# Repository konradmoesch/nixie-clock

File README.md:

# nixie-clock
6-digit nixie-clock using ESP32, IN-4 and IN-6

## dependencies
https://github.com/judge2005/Eagle-and-KiCAD-Nixie-Libs
https://github.com/Hieromon/AutoConnect

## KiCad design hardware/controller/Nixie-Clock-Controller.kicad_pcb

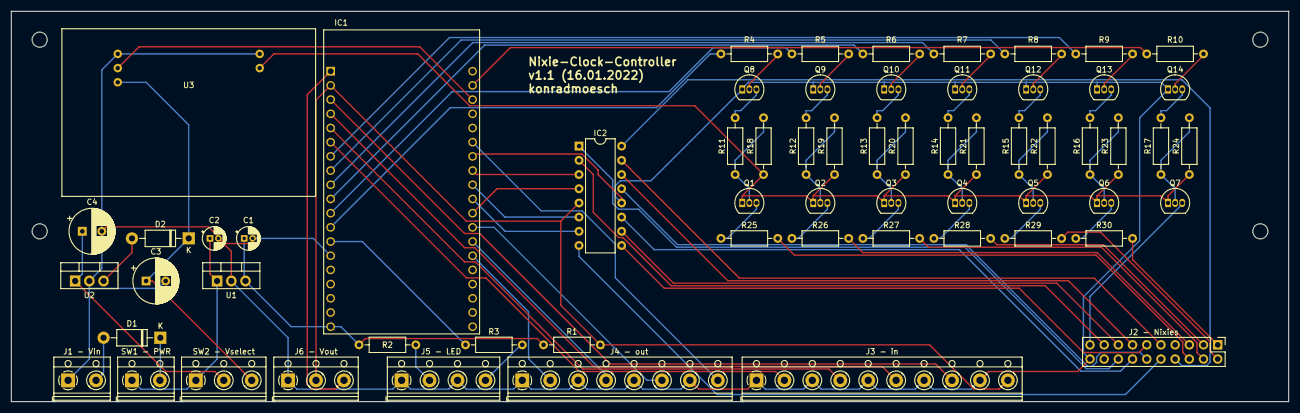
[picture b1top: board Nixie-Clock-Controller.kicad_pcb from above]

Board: 2 copper layers, 228.6 x 69.8 mm, 67 parts (0 on the bottom side), 78 nets.

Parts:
C1, C2: 10uF; CP_Radial_D4.0mm_P1.50mm
C3, C4: 100uF 50V; CP_Radial_D8.0mm_P3.50mm
D1, D2: 1N4001; D_DO-41_SOD81_P10.16mm_Horizontal
H1, H2, H3, H4: MountingHole; MountingHole_2.7mm_M2.5
IC1: ESP32-DEVKITC-V4; MODULE_ESP32-DEVKITC-32D
IC2: 74141; DIP-16_W7.62mm
J1 - Vin: 9/12-35V DC in; TerminalBlock_RND_205-00012_1x02_P5.00mm_Horizontal
J2 - Nixies: Nixies-Connector; PinHeader_2x10_P2.54mm_Vertical
J3 - in: Input; TerminalBlock_RND_205-00020_1x10_P5.00mm_Horizontal
J4 - out: Output; TerminalBlock_RND_205-00018_1x08_P5.00mm_Horizontal
J5 - LED: LEDs; TerminalBlock_RND_205-00014_1x04_P5.00mm_Horizontal
J6 - Vout: power_out; TerminalBlock_RND_205-00013_1x03_P5.00mm_Horizontal
Q1, Q2, Q3, Q4, Q5, Q6, Q7: MPSA92; TO-92_Inline
Q8, Q9, Q10, Q11, Q12, Q13, Q14: MPSA42; TO-92_Inline
R1: 1k; R_Axial_DIN0207_L6.3mm_D2.5mm_P10.16mm_Horizontal
R2, R3: 220R; R_Axial_DIN0207_L6.3mm_D2.5mm_P10.16mm_Horizontal
R4, R5, R6, R7, R8, R9, R10: 33k; R_Axial_DIN0207_L6.3mm_D2.5mm_P10.16mm_Horizontal
R11, R12, R13, R14, R15, R16, R17: 470k; R_Axial_DIN0207_L6.3mm_D2.5mm_P10.16mm_Horizontal
R18, R19, R20, R21, R22, R23, R24: 100k; R_Axial_DIN0207_L6.3mm_D2.5mm_P10.16mm_Horizontal
R25, R26, R27, R28, R29, R30: 10k; R_Axial_DIN0207_L6.3mm_D2.5mm_P10.16mm_Horizontal
SW1 - PWR: on/off; TerminalBlock_RND_205-00012_1x02_P5.00mm_Horizontal
SW2 - Vselect: in voltage select; TerminalBlock_RND_205-00013_1x03_P5.00mm_Horizontal
U1: L7805; TO-220-3_Vertical
U2: L7809; TO-220-3_Vertical
U3: NCH6300HV; NCH_6300_HV

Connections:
/a1: J2 - Nixies.1, R30.2
/a2: J2 - Nixies.2, R29.2
/a3: J2 - Nixies.3, R28.2
/a4: J2 - Nixies.4, R27.2
/a5: J2 - Nixies.5, R26.2
/a6: J2 - Nixies.6, R25.2
/c0: IC2.16 (~Q0), J2 - Nixies.8
/c1: IC2.15 (~Q1), J2 - Nixies.9
/c2: IC2.8 (~Q2), J2 - Nixies.10
/c3: IC2.9 (~Q3), J2 - Nixies.11
/c4: IC2.13 (~Q4), J2 - Nixies.12
/c5: IC2.14 (~Q5), J2 - Nixies.13
/c6: IC2.11 (~Q6), J2 - Nixies.14
/c7: IC2.10 (~Q7), J2 - Nixies.15
/c8: IC2.1 (~Q8), J2 - Nixies.16
/c9: IC2.2 (~Q9), J2 - Nixies.17
/da: J2 - Nixies.19, Q7.3 (C)
/in_1: IC1.3 (SENSOR_VP), J3 - in.8
/in_2: IC1.4 (SENSOR_VN), J3 - in.6
/in_3: IC1.5 (IO34), J3 - in.4
/in_4: IC1.6 (IO35), J3 - in.2
/led_status: J5 - LED.4, R3.2
/out_1: IC1.25 (IO21), J4 - out.8
/out_2: IC1.31 (IO16), J4 - out.6
/out_3: IC1.32 (IO4), J4 - out.4
/out_4: IC1.33 (IO0), J4 - out.2
/shdn: IC1.22 (IO22), U3.2 (SHDN)
GND: C1.2, C2.2, C3.2, C4.2, IC1.14 (GND1), IC1.26 (GND2), IC2.12 (GND), J1 - Vin.1, J2 - Nixies.20, J3 - in.1, J3 - in.3, J3 - in.5, J3 - in.7, J3 - in.9, J4 - out.1, J4 - out.3, J4 - out.5, J4 - out.7, J5 - LED.1, J5 - LED.3, J6 - Vout.1, Q8.1 (E), Q9.1 (E), Q10.1 (E), Q11.1 (E), Q12.1 (E), Q13.1 (E), Q14.1 (E), U1.2 (GND), U2.2 (GND), U3.1 (GND), U3.4 (GND)
unnamed: C1.1, IC1.19 (EXT_5V), R1.1, R2.1, U1.3 (OUT)
unnamed: C2.1, SW1 - PWR.1, SW2 - Vselect.1, U1.1 (IN)
unnamed: C3.1, D2.1 (K), SW2 - Vselect.3, U3.3 (VIN)
unnamed: C4.1, SW2 - Vselect.2, U2.1 (IN)
unnamed: D1.1 (K), SW1 - PWR.2
unnamed: D1.2 (A), J1 - Vin.2
unnamed: D2.2 (A), U2.3 (OUT)
unnamed: IC1.1 (3V3), J6 - Vout.3
unnamed: IC1.7 (IO32), R9.2
unnamed: IC1.8 (IO33), R8.2
unnamed: IC1.9 (IO25), R7.2
unnamed: IC1.10 (IO26), R6.2
unnamed: IC1.11 (IO27), R5.2
unnamed: IC1.12 (IO14), R4.2
unnamed: IC1.13 (IO12), R3.1
unnamed: IC1.21 (IO23), R10.2
unnamed: IC1.27 (IO19), IC2.3 (A)
unnamed: IC1.28 (IO18), IC2.6 (B)
unnamed: IC1.29 (IO5), IC2.7 (C)
unnamed: IC1.30 (IO17), IC2.4 (D)
unnamed: J5 - LED.2, R2.2
unnamed: Q1.1 (E), Q2.1 (E), Q3.1 (E), Q4.1 (E), Q5.1 (E), Q6.1 (E), Q7.1 (E), R18.1, R19.1, R20.1, R21.1, R22.1, R23.1, R24.1, U3.5 (HV)
unnamed: Q1.2 (B), R11.1, R18.2
unnamed: Q1.3 (C), R25.1
unnamed: Q2.2 (B), R12.1, R19.2
unnamed: Q2.3 (C), R26.1
unnamed: Q3.2 (B), R13.1, R20.2
unnamed: Q3.3 (C), R27.1
unnamed: Q4.2 (B), R14.1, R21.2
unnamed: Q4.3 (C), R28.1
unnamed: Q5.2 (B), R15.1, R22.2
unnamed: Q5.3 (C), R29.1
unnamed: Q6.2 (B), R16.1, R23.2
unnamed: Q6.3 (C), R30.1
unnamed: Q7.2 (B), R17.1, R24.2
unnamed: Q8.2 (B), R4.1
unnamed: Q8.3 (C), R11.2
unnamed: Q9.2 (B), R5.1
unnamed: Q9.3 (C), R12.2
unnamed: Q10.2 (B), R6.1
unnamed: Q10.3 (C), R13.2
unnamed: Q11.2 (B), R7.1
unnamed: Q11.3 (C), R14.2
unnamed: Q12.2 (B), R8.1
unnamed: Q12.3 (C), R15.2
unnamed: Q13.2 (B), R9.1
unnamed: Q13.3 (C), R16.2
unnamed: Q14.2 (B), R10.1
unnamed: Q14.3 (C), R17.2
VCC: IC1.2 (EN), IC2.5 (VCC), J3 - in.10, J6 - Vout.2, R1.2

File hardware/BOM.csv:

Reference,Quantity,Value,Footprint,Manufacturer,Shop,Partnum,Price,Total Price
C1 C2 ,2,10uF,"E-Cap, radial, 10μF, 25V, RM 1.5 20%",-,Conrad,1325870,"0,05 €","0,10 €"
C3 C4 ,2,100uF 50V,"E-Cap, radial, 100μF, 50 V, RM 5, 105°C, 6000 h, 20% ",-,Reichelt,FR-A 100U 50,"0,26 €","0,52 €"
D1 D2 ,2,1N4001,"Rectifier diode DO41, 50 V, 1 A",-,Reichelt,1N4001,"0,02 €","0,04 €"
IC1 ,1,ESP32-DEVKITC-V4,AZDelivery ESP32 Dev Kit C V4,Espressif Systems,Amazon,B07Z83MF5W,"11,99 €","11,99 €"
IC1 ,2,1x19 pin,"Socket, 20-pin, single row, spacing 2.54, straight",-,Reichelt,SPL 20,"0,46 €","0,92 €"
IC2 ,1,74141,6x SN74141N K155ID1 bcd to decimal decoder/driver,-,Ebay,154468654882,"1,67 €","1,67 €"
IC2 ,1,16 pin,IC Socket 16 pin,-,Reichelt,MPE 001-1-016-3,"0,37 €","0,37 €"
J1 ,1,9/12-35V DC in,Terminal Block 2 pin,-,Amazon,B08G1BSP8D,"8,99 €","8,99 €"
J2 ,1,Nixies-Connector,BKL Electronic 10120560 pin header RM 2.54 mm,-,Conrad,741766,"0,50 €","0,50 €"
J3 ,1,Input,Terminal Block 10 pin,-,-,-,,"0,00 €"
J4 ,1,Output,Terminal Block 8 pin ,-,-,-,,"0,00 €"
J5 ,1,LEDs,Terminal Block 4 pin,-,-,-,,"0,00 €"
J6 ,1,power_out,Terminal Block 3 pin,-,-,-,,"0,00 €"
Q2 Q3 Q4 Q5 Q6 Q7 Q8 ,7,MPSA92,Transistor PNP TO-92 300 V 0.5 A 0.625 W,-,Reichelt,MPSA 92,"0,07 €","0,49 €"
Q1 Q9 Q10 Q11 Q12 Q13 Q14 ,7,MPSA42,NPN TO-92 transistor 300V 0.5A 0.625W,-,Reichelt,MPSA 42,"0,05 €","0,36 €"
R1 ,1,1k,"Carbon film resistor 1/4 W, 5%, 1.0 kilo-ohms",-,Reichelt,"1/4W 1,0K","0,10 €","0,10 €"
R11 R12 R13 R14 R15 R16 R17 ,7,470k,"Carbon film resistor 1/4 W, 5%, 470 kOhm",-,Reichelt,1/4W 470K,"0,10 €","0,70 €"
R18 R19 R20 R21 R22 R23 R24 ,7,100k,"Carbon film resistor 1/4 W, 5%, 100 kOhm",-,Reichelt,1/4W 100K,"0,10 €","0,70 €"
R2 R3 ,2,220R,"Carbon film resistor 1/4 W, 5%, 220 ohm",-,Reichelt,1/4W 220,"0,10 €","0,20 €"
R25 R26 R27 R28 R29 R30 ,6,10k,,-,Reichelt,1/4W 10K,"0,10 €","0,60 €"
R4 R5 R6 R7 R8 R9 R10 ,7,33k,"Carbon film resistor 1/4 W, 5%, 33 kOhm",-,Reichelt,1/4W 33K,"0,10 €","0,70 €"
SW1 ,1,on/off,Terminal Block 2 pin,-,-,-,,"0,00 €"
SW2 ,1,in voltage select,Terminal Block 3 pin,-,-,-,,"0,00 €"
U1 ,1,L7805 CV,"Voltage regulator, fixed, +5V, 1.5A, 4%, TO-220",-,Reichelt,L7805 CV,"0,36 €","0,36 €"
U2 ,1,L7809CV STM,"Voltage regulator, fixed, +9V, 1.5A, 4%, TO-220",-,Reichelt,L7809CV STM,"0,30 €","0,30 €"
U3 ,1,NCH6300HV,NCH 6300 HV nixie power supply,-,Aliexpress,1005002739180969,"22,99 €","22,99 €"
,,,,,,,,
J1 ,1,Nixies-Connector,"Pin connector, 20-pin, with interlock, angled",-,Reichelt,PSL 20W,"0,31 €","0,31 €"
N1 N2 N3 N4 N5 N6 ,6,IN-4,"IN-4 NIXIE Tubes 6 pcs. For DIY Nixie Clock. NEW, NOS. SAME DATE, NEVER USED",-,Ebay,255154709291,"5,00 €","30,00 €"
N7 N8 N9 N10 ,4,IN-6,6x IN-6 Nixie Lamp Soviet USSR Neon Tube Lot of 6pcs #703,-,Ebay,252669021825,"1,25 €","5,00 €"
R1 R2 R3 R4 R5 R6 ,6,5k,"Carbon film resistor 1/4 W, 5%, 5 kOhm",-,Reichelt,"1/4W 5,0K","0,10 €","0,60 €"
R7 R8 R9 R10 ,4,15k,"Carbon film resistor 1/4 W, 5%, 15 kOhm",-,Reichelt,2/4W 15K,"0,10 €","0,40 €"
,,,,,,,,
Spacers,12,,"Spacers M3, size as needed",-,Reichelt,VT DA 12MM/VT DA 30MM,"0,32 €","3,84 €"
Socket power in,?,?,?,?,?,?,?,?
Buttons/Switches,?,?,?,?,?,?,?,?
LED red,2,-,"LED, 5 mm, leaded, red, 563 mcd, 19°",-,Reichelt,LED 5MM RT,"0,07 €","0,14 €"
LED socket,2,-,"Installation socket, 5 mm, external reflector, black",-,Reichelt,EBF A-5 S,"1,10 €","2,20 €"
Ribbon cable,1,-,"Flat ribbon cable AWG 28, 24-pin, grey, 3-m ring",-,Reichelt,AWG28-24G 3M,"7,99 €","7,99 €"
IDC Socket,2,-,20-pin IDC socket with strain relief ,-,Reichelt,PFL 20,"0,35 €","0,70 €"
Case,1,-,Ziegelform,-,-,-,"11,95 €","11,95 €"
,,,,,,,,
,,,,,,,Total,"115,73 €"

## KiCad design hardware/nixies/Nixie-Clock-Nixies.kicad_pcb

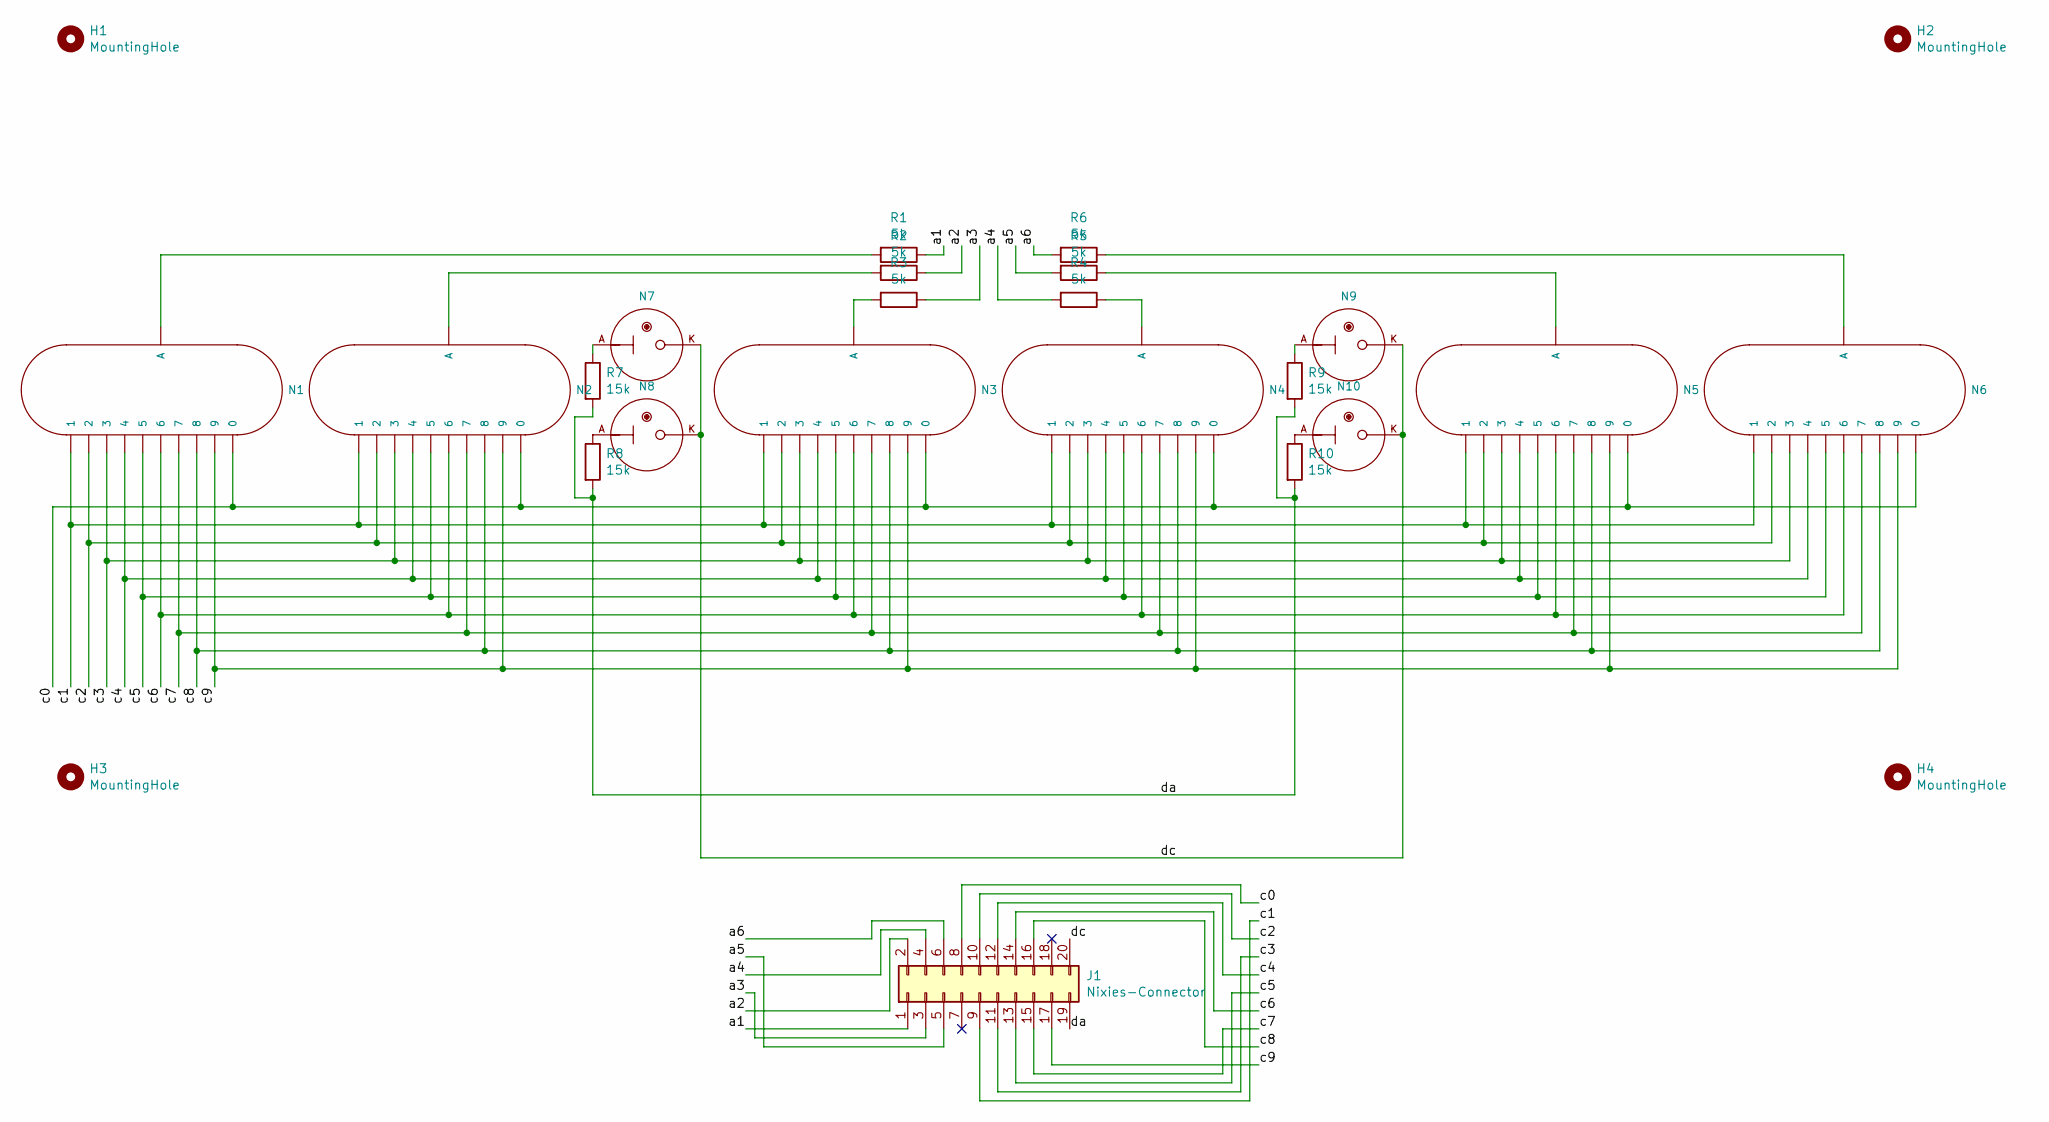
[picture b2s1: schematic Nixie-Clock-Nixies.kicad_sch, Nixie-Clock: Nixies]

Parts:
H1, H2, H3, H4: MountingHole; MountingHole_2.7mm_M2.5
J1: Nixies-Connector; PinHeader_2x10_P2.54mm_Horizontal_with_Interlock
N1, N2, N3, N4, N5, N6: IN-4; nixies-us-IN-4-DSUB
N7, N8, N9, N10: IN-6; nixies-us-IN-6
R1, R2, R3, R4, R5, R6: 5k; R_Axial_DIN0207_L6.3mm_D2.5mm_P10.16mm_Horizontal
R7, R8, R9, R10: 15k; R_Axial_DIN0207_L6.3mm_D2.5mm_P10.16mm_Horizontal

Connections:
/a1: J1.1, R1.1
/a2: J1.2, R2.1
/a3: J1.3, R3.1
/a4: J1.4, R4.2
/a5: J1.5, R5.2
/a6: J1.6, R6.2
/c0: J1.8, N1.0, N2.0, N3.0, N4.0, N5.0, N6.0
/c1: J1.9, N1.1, N2.1, N3.1, N4.1, N5.1, N6.1
/c2: J1.10, N1.2, N2.2, N3.2, N4.2, N5.2, N6.2
/c3: J1.11, N1.3, N2.3, N3.3, N4.3, N5.3, N6.3
/c4: J1.12, N1.4, N2.4, N3.4, N4.4, N5.4, N6.4
/c5: J1.13, N1.5, N2.5, N3.5, N4.5, N5.5, N6.5
/c6: J1.14, N1.6, N2.6, N3.6, N4.6, N5.6, N6.6
/c7: J1.15, N1.7, N2.7, N3.7, N4.7, N5.7, N6.7
/c8: J1.16, N1.8, N2.8, N3.8, N4.8, N5.8, N6.8
/c9: J1.17, N1.9, N2.9, N3.9, N4.9, N5.9, N6.9
/da: J1.19, R7.2, R8.2, R9.2, R10.2
/dc: J1.20, N7.K, N8.K, N9.K, N10.K
unnamed: N1.A3 (A), R1.2
unnamed: N2.A3 (A), R2.2
unnamed: N3.A3 (A), R3.2
unnamed: N4.A3 (A), R4.1
unnamed: N5.A3 (A), R5.1
unnamed: N6.A3 (A), R6.1
unnamed: N7.A, R7.1
unnamed: N8.A, R8.1
unnamed: N9.A, R9.1
unnamed: N10.A, R10.1

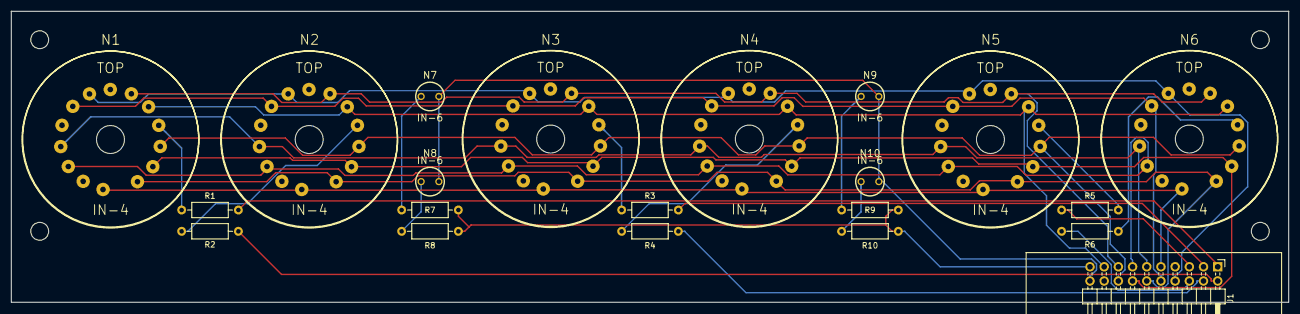
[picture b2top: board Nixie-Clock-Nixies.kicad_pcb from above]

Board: 2 copper layers, 228.6 x 52.1 mm, 25 parts (0 on the bottom side), 28 nets.

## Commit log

2021-12-23 Add hardware schematics
2021-12-23 Add first pieces of code
2021-12-23 Add some nixie control stuff
2021-12-24 Switch to platform.io and Clion
2021-12-24 Edit monitor baud rate
2021-12-25 Add some pio check tweaks
2021-12-25 Remove autorouting files
2021-12-25 Add routing files and pdf to .gitignore
2021-12-25 Add screw terminals for I/O, Improve PCB layout
2021-12-25 Add Mounting Holes to PCB, Improve Routing, Add power pin header, Use correct connector footprint
2021-12-25 Fix libraries used in Nixie-Clock-Nixies
2021-12-25 Fix libraries used in Nixie-Clock-Controller
2021-12-25 Add parts library
2021-12-25 Rename folder
2021-12-28 Shrink pcbs
2021-12-28 Improve text label positioning
2021-12-28 Change Mountingholes to M3
2021-12-30 Fix path error
2021-12-30 Fix text labels
2021-12-30 Fix nixie drill hole size
2022-01-02 Use AutoConnect, Add LCD, Restructure everything
2022-01-02 Add error handling when config invalid
2022-01-02 Add NixieController
2022-01-03 Add BOM
2022-01-03 Fix uF in BOM, Fix 74141 count
2022-01-03 Add some idea files to gitignore
2022-01-03 Add another attempt of validating stored config data
2022-01-03 Add nixie clock display feature
2022-01-03 Fix wrong pin mapping on U3
2022-01-04 Move nixie control code to other core, Add some very basic ghosting prevention
2022-01-04 Move to Kicad 6
2022-01-04 Add newline at the end of file
2022-01-16 Fix pin Layout again
2022-01-16 fix wrong transistor connections
2022-01-16 Improve transistor numbering
2022-01-16 Add version text
2022-01-16 Update version
2022-01-16 Add date output
2022-01-17 Improve labels
2022-02-24 Improve bcd conversion
2022-02-24 Refactor classes and imports
2022-02-24 Add version, Impl togglePowerSupply, OTA and webSerial (commented out), Improve date display
2022-03-03 Impl information provider and -proxy, improve class structure
2022-03-23 Test GitHub actions
2022-03-23 update working dir
